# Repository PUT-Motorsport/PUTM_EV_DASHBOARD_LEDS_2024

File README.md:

# Dashboard LEDs

This project contains design for the dashboard LED panel. It includes the following components:

- LEDs PCB,
- Connector PCB (to connect the LEDs PCB to the dashboard).

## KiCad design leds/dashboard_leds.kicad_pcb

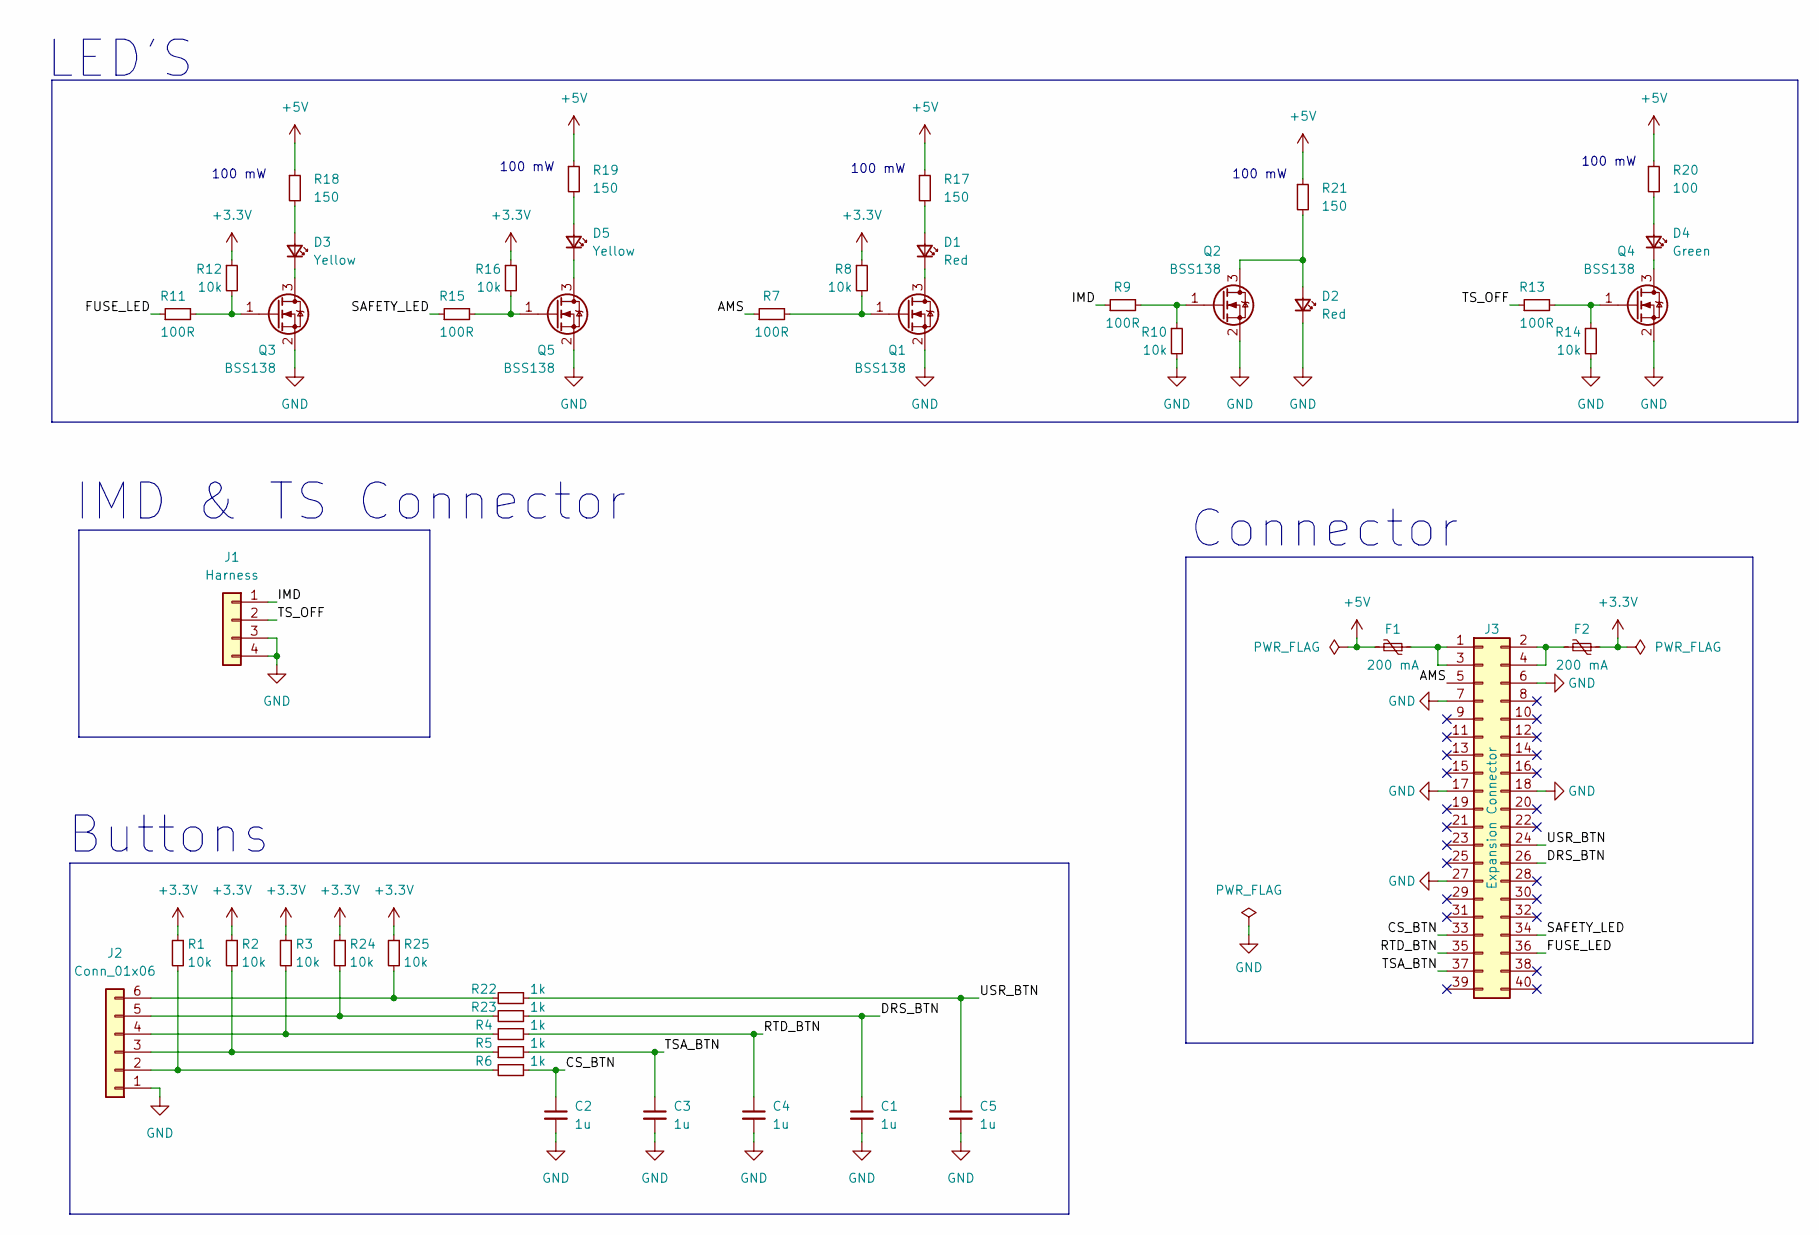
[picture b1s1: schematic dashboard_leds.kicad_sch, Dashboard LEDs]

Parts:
C1, C2, C3, C4, C5: 1u; C_0603_1608Metric
D1, D2: Red; LED_PLCC-2_3.4x3.0mm_AK
D3, D5: Yellow; LED_PLCC-2_3.4x3.0mm_AK
D4: Green; LED_PLCC-2_3.4x3.0mm_AK
F1, F2: 200 mA; Fuse_1206_3216Metric
J1: Harness; Molex_53261-0471
J2: Conn_01x06; SolderWire-0.15sqmm_1x06_P4mm_D0.5mm_OD1.5mm_Relief
J3: Expansion Connector; PinSocket_2x20_P1.27mm_Vertical_SMD
Q1, Q2, Q3, Q4, Q5: BSS138; SOT-23
R1, R2, R3, R8, R10, R12, R14, R16, R24, R25: 10k; R_0603_1608Metric
R4, R5, R6, R22, R23: 1k; R_0603_1608Metric
R7, R9, R11, R13, R15: 100R; R_0603_1608Metric
R17, R18, R19, R21: 150; R_1206_3216Metric
R20: 100; R_1206_3216Metric

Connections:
+3.3V: F2.1, R1.1, R2.1, R3.1, R8.1, R12.1, R16.1, R24.1, R25.1
+5V: F1.2, R17.1, R18.1, R19.1, R20.1, R21.1
/AMS: J3.5, R7.1
/CS_BTN: C2.1, J3.33, R6.1
/DRS_BTN: C1.1, J3.26, R23.1
/FUSE_LED: J3.36, R11.1
/IMD: J1.1, R9.1
/RTD_BTN: C4.1, J3.35, R4.1
/SAFETY_LED: J3.34, R15.1
/TSA_BTN: C3.1, J3.37, R5.2
/TS_OFF: J1.2, R13.1
/USR_BTN: C5.1, J3.24, R22.1
GND: C1.2, C2.2, C3.2, C4.2, C5.2, D2.1 (K), J1.3, J1.4, J2.1, J3.6, J3.7, J3.17, J3.18, J3.27, Q1.2 (S), Q2.2 (S), Q3.2 (S), Q4.2 (S), Q5.2 (S), R10.2, R14.2
unnamed: D1.2 (A), R17.2
unnamed: D1.1 (K), Q1.3 (D)
unnamed: D2.2 (A), Q2.3 (D), R21.2
unnamed: D3.2 (A), R18.2
unnamed: D3.1 (K), Q3.3 (D)
unnamed: D4.2 (A), R20.2
unnamed: D4.1 (K), Q4.3 (D)
unnamed: D5.2 (A), R19.2
unnamed: D5.1 (K), Q5.3 (D)
unnamed: J2.2, R1.2, R6.2
unnamed: J2.3, R2.2, R5.1
unnamed: J2.4, R3.2, R4.2
unnamed: J2.5, R23.2, R24.2
unnamed: J2.6, R22.2, R25.2
unnamed: F1.1, J3.1, J3.3
unnamed: F2.2, J3.2, J3.4
unnamed: Q1.1 (G), R7.2, R8.2
unnamed: Q2.1 (G), R9.2, R10.1
unnamed: Q3.1 (G), R11.2, R12.2
unnamed: Q4.1 (G), R13.2, R14.1
unnamed: Q5.1 (G), R15.2, R16.2

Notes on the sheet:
100 mW
Connector
LED'S
Buttons
IMD & TS Connector

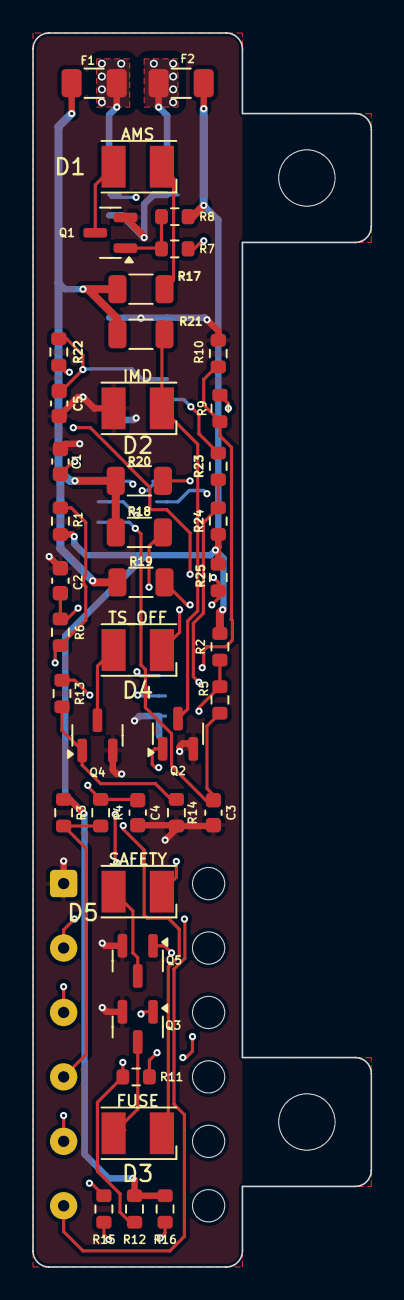
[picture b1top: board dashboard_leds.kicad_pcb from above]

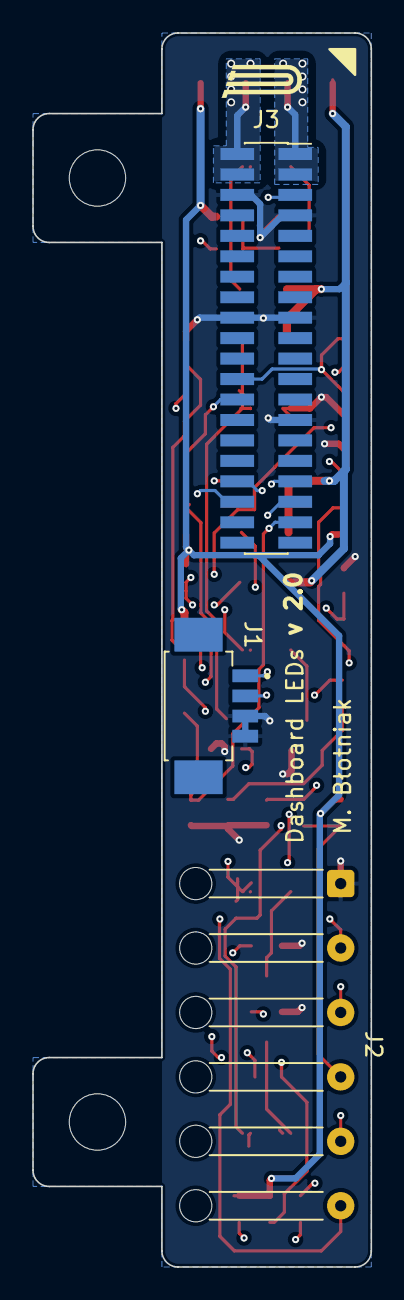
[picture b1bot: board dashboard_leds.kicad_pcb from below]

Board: 4 copper layers, 21.0 x 76.6 mm, 45 parts (3 on the bottom side), 34 nets.

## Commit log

2024-05-29 Fix connector wiring
2024-06-05 Update button labels
2024-06-25 Add display documentation
2024-11-27 Edit the scheme
2024-11-30 Edit PCB layout
    *without zone
2024-11-30 Add zones and some changes
2024-11-30 Fixing bugs on PCB
2024-11-30 Editing zones and minor changes
2024-12-12 Complete change of design
    Change from 2 layer to 4 layer, add bigger resistors, change diodes
2024-12-14 Changing the path guidance
2025-01-12 Updating one resistor value on pcb
